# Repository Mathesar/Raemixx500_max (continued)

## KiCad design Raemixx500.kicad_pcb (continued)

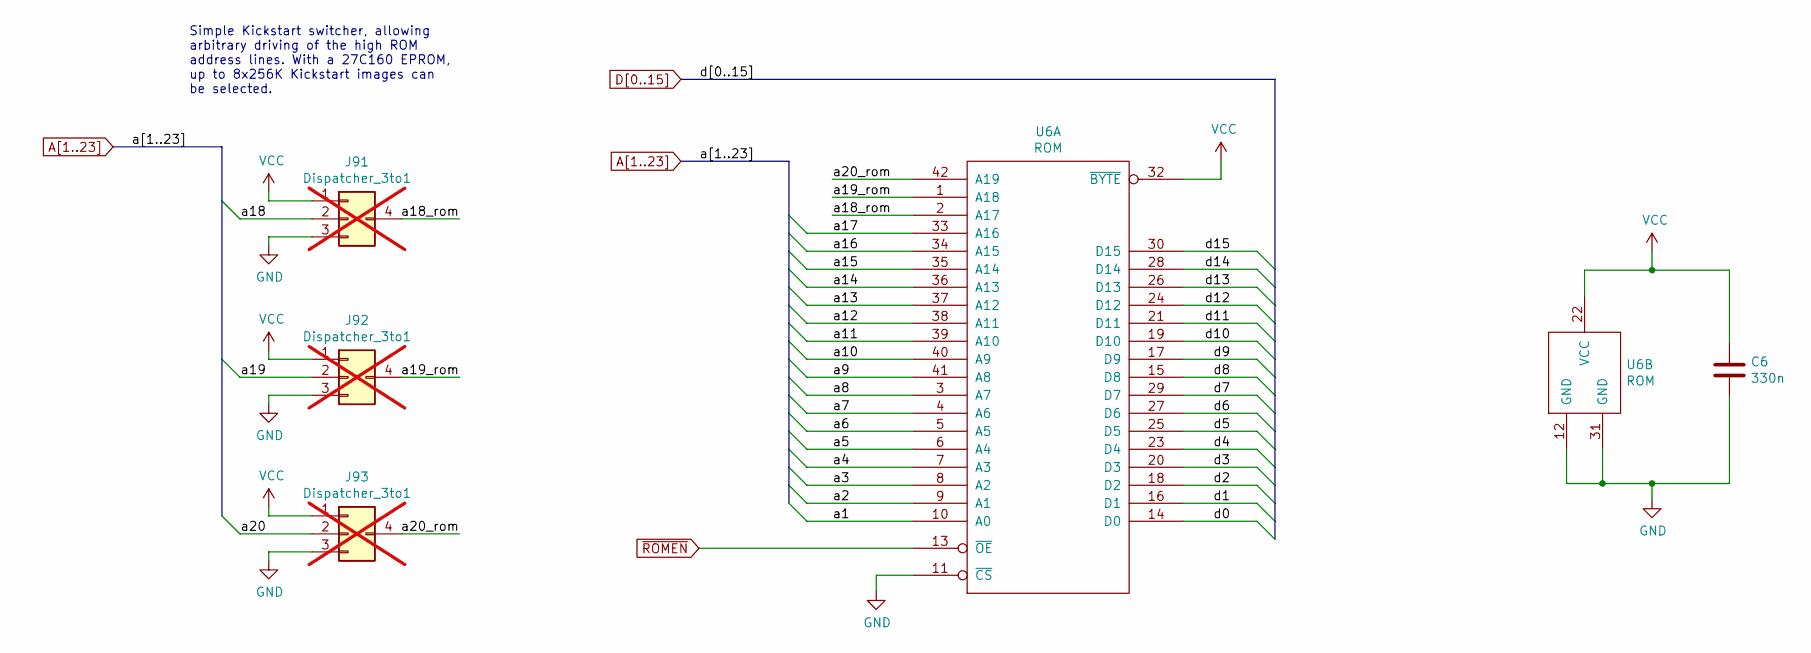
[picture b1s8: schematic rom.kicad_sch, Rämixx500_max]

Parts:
C6: 330n; C_Axial_L6.3mm_D2.5mm_P10.16mm; MFG Part Num C440C334K5R5TA7200; Mouser 80-C440C334K5R-TR
J91, J92, J93: Dispatcher_3to1; not fitted
U6: ROM; DIP-42_W15.24mm_Socket_LongPads; MFG Part Num 4842-6000-CP; Mouser 517-4842-6000-CP

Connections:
/Kickstart ROM/a18_rom: J91.4 (Out), U6.2 (A17)
/Kickstart ROM/a19_rom: J92.4 (Out), U6.1 (A18)
/Kickstart ROM/a20_rom: J93.4 (Out), U6.42 (A19)
A1: U6.10 (A0); also elsewhere on the board
A2: U6.9 (A1); also elsewhere on the board
A3: U6.8 (A2); also elsewhere on the board
A4: U6.7 (A3); also elsewhere on the board
A5: U6.6 (A4); also elsewhere on the board
A6: U6.5 (A5); also elsewhere on the board
A7: U6.4 (A6); also elsewhere on the board
A8: U6.3 (A7); also elsewhere on the board
A9: U6.41 (A8); also elsewhere on the board
A10: U6.40 (A9); also elsewhere on the board
A11: U6.39 (A10); also elsewhere on the board
A12: U6.38 (A11); also elsewhere on the board
A13: U6.37 (A12); also elsewhere on the board
A14: U6.36 (A13); also elsewhere on the board
A15: U6.35 (A14); also elsewhere on the board
A16: U6.34 (A15); also elsewhere on the board
A17: U6.33 (A16); also elsewhere on the board
A18: J91.2 (In_2); also elsewhere on the board
A19: J92.2 (In_2); also elsewhere on the board
A20: J93.2 (In_2); also elsewhere on the board
D0: U6.14 (D0); also elsewhere on the board
D1: U6.16 (D1); also elsewhere on the board
D2: U6.18 (D2); also elsewhere on the board
D3: U6.20 (D3); also elsewhere on the board
D4: U6.23 (D4); also elsewhere on the board
D5: U6.25 (D5); also elsewhere on the board
D6: U6.27 (D6); also elsewhere on the board
D7: U6.29 (D7); also elsewhere on the board
D8: U6.15 (D8); also elsewhere on the board
D9: U6.17 (D9); also elsewhere on the board
D10: U6.19 (D10); also elsewhere on the board
D11: U6.21 (D11); also elsewhere on the board
D12: U6.24 (D12); also elsewhere on the board
D13: U6.26 (D13); also elsewhere on the board
D14: U6.28 (D14); also elsewhere on the board
D15: U6.30 (D15); also elsewhere on the board
GND: C6.2, J91.3 (In_3), J92.3 (In_3), J93.3 (In_3), U6.11 (~CS), U6.12 (GND), U6.31 (GND); also elsewhere on the board
VCC: C6.1, J91.1 (In_1), J92.1 (In_1), J93.1 (In_1), U6.22 (VCC), U6.32 (~BYTE); also elsewhere on the board
~ROMEN: U6.13 (~OE); also elsewhere on the board

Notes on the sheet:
Simple Kickstart switcher, allowing arbitrary driving of the high ROM address lines. With a 27C160 EPROM, up to 8x256K Kickstart images can be selected.

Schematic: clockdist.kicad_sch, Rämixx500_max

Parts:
C33: 10n; C_Axial_L6.3mm_D2.5mm_P10.16mm; MFG Part Num C410C103K1R5TA; Mouser 80-C410C103K1R
E102, E103, E106, E107, E108: 47p; C_Axial_L9.0mm_D3.2mm_P12.70mm; MFG Part Num A470J15C0GF5TAA; Mouser 594-A470J15C0GF5TAA
E104, E105: 68; EMI_Filter_Long; MFG Part Num MFR-25FBF52-68R; Mouser 603-MFR-25FBF52-68R
E109, E791, E792, E793, E794: 47p; C_Axial_L6.3mm_D2.5mm_P10.16mm; MFG Part Num A470J15C0GF5TAA; Mouser 594-A470J15C0GF5TAA
E407: 10n; EMI_Filter_Short; MFG Part Num DSS1NB32A103Q91A; Mouser 81-DSS1NB32A103Q91A
RP103: 39; R_Array_SIP10; MFG Part Num 4610X-102-390LF; Mouser 652-4610X-2LF-39
U33: 74F258; DIP-16_W7.62mm_LongPads; MFG Part Num SN74F258N; Mouser 595-SN74F258N

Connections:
7MHZ: E103.1; also elsewhere on the board
7MHZ_A: E794.1; also elsewhere on the board
CCK: E108.1, U33.5, U33.6; also elsewhere on the board
CCKQ: E107.1, U33.10, U33.11; also elsewhere on the board
CDAC: E793.1, RP103.4 (R2.2); also elsewhere on the board
GND: C33.2, E102.2, E103.2, E104.2, E105.2, E106.2, E107.2, E108.2, E109.2, E407.2, E791.2, E792.2, E793.2, E794.2, U33.8 (GND), U33.15 (OE); also elsewhere on the board
unnamed: RP103.3 (R2.1), U33.4
unnamed: E104.1, RP103.5 (R3.1), U33.7
unnamed: E105.1, RP103.7 (R4.1), U33.9
unnamed: C33.1, E407.3, U33.16 (VCC)
VCC: E407.1; also elsewhere on the board
~CCKQ_A: E105.3, E109.1; also elsewhere on the board
~CCKQ: E791.1, RP103.8 (R4.2); also elsewhere on the board
~CCK_A: E102.1, E104.3; also elsewhere on the board
~CCK: E792.1, RP103.6 (R3.2); also elsewhere on the board
~CDAC: E106.1, U33.2, U33.3; also elsewhere on the board
~XCLKEN: U33.1 (S); also elsewhere on the board

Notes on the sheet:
FCC GOOBERS

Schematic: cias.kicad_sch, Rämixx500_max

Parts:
C7, C8: 10n; C_Axial_L6.3mm_D2.5mm_P10.16mm; MFG Part Num C410C103K1R5TA; Mouser 80-C410C103K1R
C39, C713: 10n; C_Axial_L9.0mm_D3.2mm_P12.70mm; MFG Part Num C410C103K1R5TA; Mouser 80-C410C103K1R
C42: 330n; C_Axial_L6.3mm_D2.5mm_P10.16mm; MFG Part Num C440C334K5R5TA7200; Mouser 80-C440C334K5R-TR
C501, C502: 330n; C_Axial_L9.0mm_D3.2mm_P12.70mm; MFG Part Num C440C334K5R5TA7200; Mouser 80-C440C334K5R-TR
C711: 100n; C_Axial_L9.0mm_D3.2mm_P12.70mm; MFG Part Num A104K15X7RF5TAA; Mouser 594-A104K15X7RF5TAA
C712: 10u; CP_Radial_D5.0mm_P2.50mm; MFG Part Num ECA-1EM100I; Mouser 667-ECA-1EM100I
CN6: SERIAL_DB25M; DB_25M; MFG Part Num L717SDB25PA4CH4F; Mouser 523-L717SDB25PA4CH4F
CN7: PARALLEL_DB25F; DB_25F; MFG Part Num L77SDB25SA4CH4F; Mouser 523-L77SDB25SA4CH4F
CN13: KEYBOARD; Keyboard_Connector; MFG Part Num 10129378-908003BLF; Mouser 649-1012937890803BLF
D501: 1N4148; D_DO-35_SOD27_P12.70mm_Horizontal; MFG Part Num 1N4148TR; Mouser 512-1N4148TR
E501, E502, E503: 47 1/2W; EMI_Filter_Longer; MFG Part Num PR01000104709JA500; Mouser 594-PR01000104709JA5
E511, E512, E513, E514, E515, E516, E517, E518, E519, E521, E522, E523, E524, E631, E632: 100p; EMI_Filter_Short; MFG Part Num DSS1NB32A101Q91A; Mouser 81-DSS1NB32A101Q91A
E520, E531, E533, E535, E536, E537, E538: 470p; EMI_Filter_Short; MFG Part Num DSS1NB32A471Q91A; Mouser 81-DSS1NB32A471Q91A
E532, E534: 150p; EMI_Filter_Short; MFG Part Num DSS1NB32A151Q91A; Mouser 81-DSS1NB32A151Q91A
J90: DRIVE_SWITCHER; DriveSwitchHeader; not fitted
J99: HD_ACT; PinHeader_1x02_P2.54mm_Vertical; MFG Part Num 10129378-902003BLF; Mouser 649-1012937890203BLF
JP1: Jumper_2_Bridged; Jumper2-Bridged; MFG Part Num SKIP
JP7B1: Jumper_3_Bridged23; Jumper3-Bridged23; MFG Part Num SKIP
Q501, Q504, Q711: 2N3904; TO-92L_Inline_Wide; MFG Part Num 2N3904BU; Mouser 512-2N3904BU
Q502, Q503: 2N3906; TO-92L_Inline_Wide; MFG Part Num 2N3906BU; Mouser 512-2N3906BU
R109: 68; R_Axial_DIN0309_L9.0mm_D3.2mm_P12.70mm_Horizontal; MFG Part Num MFR-25FBF52-68R; Mouser 603-MFR-25FBF52-68R
R501, R504, R505, R506, R509, R510: 10K; R_Axial_DIN0309_L9.0mm_D3.2mm_P12.70mm_Horizontal; MFG Part Num MFR-25FBF52-10K; Mouser 603-MFR-25FBF52-10K
R502: 2.7k; R_Axial_DIN0309_L9.0mm_D3.2mm_P12.70mm_Horizontal; MFG Part Num MFR-25FBF52-2K7; Mouser 603-MFR-25FBF52-2K7
R503, R508: 4.7k; R_Axial_DIN0309_L9.0mm_D3.2mm_P12.70mm_Horizontal; MFG Part Num MFR-25FBF52-4K7; Mouser 603-MFR-25FBF52-4K7
R507: 100; R_Axial_DIN0309_L9.0mm_D3.2mm_P12.70mm_Horizontal; MFG Part Num MFR-25FBF52-100R; Mouser 603-MFR-25FBF52-100R
R711: 1M; R_Axial_DIN0309_L9.0mm_D3.2mm_P12.70mm_Horizontal; MFG Part Num MFR-25FBF52-1M; Mouser 603-MFR-25FBF52-1M
R712: 47k; R_Axial_DIN0309_L9.0mm_D3.2mm_P12.70mm_Horizontal; MFG Part Num MFR-25FBF52-47K; Mouser 603-MFR-25FBF52-47K
R713: 1k; R_Axial_DIN0309_L9.0mm_D3.2mm_P12.70mm_Horizontal; MFG Part Num MFR-25FBF52-1K; Mouser 603-MFR-25FBF52-1K
RP501: 10K; R_Array_SIP10; MFG Part Num 4610X-101-103LF; Mouser 652-4610X-1LF-10K
U7, U8: VIA_8520; DIP-40_W15.24mm_Socket_LongPads; MFG Part Num 4840-6000-CP; Mouser 517-4840-6000-CP
U38: MC1488; DIP-14_W7.62mm_LongPads; MFG Part Num SN75C188N; Mouser 595-SN75C188N
U39: MC1489; DIP-14_W7.62mm_LongPads; MFG Part Num SN75C189N; Mouser 595-SN75C189N
U42: NE555; DIP-8_W7.62mm_LongPads; MFG Part Num SA555P; Mouser 595-SA555P

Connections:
+12V: E502.1, U38.14 (VCC); also elsewhere on the board
-12V: E503.1, U38.1 (VEE); also elsewhere on the board
/Parallel & Serial/+v: CN6.9, E502.3
/Parallel & Serial/-v: CN6.10, E503.3
/Parallel & Serial/cd: CN6.8, E537.3
/Parallel & Serial/clock: CN13.1, E632.1
/Parallel & Serial/cts: CN6.5, E535.3
/Parallel & Serial/data: CN13.2, E631.1
/Parallel & Serial/dsr: CN6.6, E536.3
/Parallel & Serial/dtr: CN6.20, E531.3
/Parallel & Serial/inuse: CN13.8, Q503.3 (C)
/Parallel & Serial/pp0: E512.1, U7.10 (PB0)
/Parallel & Serial/pp1: E513.1, U7.11 (PB1)
/Parallel & Serial/pp2: E514.1, U7.12 (PB2)
/Parallel & Serial/pp3: E515.1, U7.13 (PB3)
/Parallel & Serial/pp4: E516.1, U7.14 (PB4)
/Parallel & Serial/pp5: E517.1, U7.15 (PB5)
/Parallel & Serial/pp6: E518.1, U7.16 (PB6)
/Parallel & Serial/pp7: E519.1, U7.17 (PB7)
/Parallel & Serial/rts: CN6.4, E533.3
/Parallel & Serial/rxd: CN6.3, E534.3
/Parallel & Serial/sel0_out: J90.1, J90.2, U8.13 (PB3)
/Parallel & Serial/sel1_out: J90.5, J90.6, U8.14 (PB4)
/Parallel & Serial/status: CN13.7, Q502.3 (C), R507.1
/Parallel & Serial/txd: CN6.2, E532.3
/Parallel & Serial/~auto: CN7.14, E501.3
/Parallel & Serial/~init: CN7.16, E520.3
A8: U7.38 (RS0), U8.38 (RS0); also elsewhere on the board
A9: U7.37 (RS1), U8.37 (RS1); also elsewhere on the board
A10: U7.36 (RS2), U8.36 (RS2); also elsewhere on the board
A11: U7.35 (RS3), U8.35 (RS3); also elsewhere on the board
AUDIN: C501.1; also elsewhere on the board
AUDOUT: C502.2; also elsewhere on the board
D0: U7.33 (D0); also elsewhere on the board
D1: U7.32 (D1); also elsewhere on the board
D2: U7.31 (D2); also elsewhere on the board
D3: U7.30 (D3); also elsewhere on the board
D4: U7.29 (D4); also elsewhere on the board
D5: U7.28 (D5); also elsewhere on the board
D6: U7.27 (D6); also elsewhere on the board
D7: U7.26 (D7); also elsewhere on the board
D8: U8.33 (D0); also elsewhere on the board
D9: U8.32 (D1); also elsewhere on the board
D10: U8.31 (D2); also elsewhere on the board
D11: U8.30 (D3); also elsewhere on the board
D12: U8.29 (D4); also elsewhere on the board
D13: U8.28 (D5); also elsewhere on the board
D14: U8.27 (D6); also elsewhere on the board
D15: U8.26 (D7); also elsewhere on the board
DIR: U8.11 (PB1); also elsewhere on the board
E: R109.2; also elsewhere on the board
GND: C7.2, C8.2, C39.2, C42.2, C711.2, C712.2, C713.2, CN6.0 (PAD), CN6.7, CN7.0 (PAD), CN7.17, CN7.18, CN7.19, CN7.20, CN7.21, CN7.22, CN7.23, CN7.24, CN7.25, CN13.6, D501.2 (A), E501.2, E502.2, E503.2, E511.2, E512.2, E513.2, E514.2, E515.2, E516.2, E517.2, E518.2, E519.2, E520.2, E521.2, E522.2, E523.2, E524.2, E531.2, E532.2, E533.2, E534.2, E535.2, E536.2, E537.2, E538.2, E631.2, E632.2, Q501.1 (E), Q504.1 (E), Q711.1 (E), R501.1, R509.2, U7.1 (GND), U8.1 (GND), U38.7 (GND), U39.7 (GND), U42.1 (GND); also elsewhere on the board
unnamed: C502.1, CN6.11
unnamed: C501.2, CN6.18
unnamed: CN6.22, E538.3
unnamed: CN7.1, E511.3
unnamed: CN7.2, E512.3
unnamed: CN7.3, E513.3
unnamed: CN7.4, E514.3
unnamed: CN7.5, E515.3
unnamed: CN7.6, E516.3
unnamed: CN7.7, E517.3
unnamed: CN7.8, E518.3
unnamed: CN7.9, E519.3
unnamed: CN7.10, E521.3
unnamed: CN7.11, E522.3
unnamed: CN7.12, E523.3
unnamed: CN7.13, E524.3
unnamed: D501.1 (K), Q501.2 (B), R501.2, R502.2
unnamed: E538.1, R502.1
unnamed: J99.1, Q504.3 (C), R508.2
unnamed: J99.2, R510.2
unnamed: JP1.1 (A), Q711.3 (C)
unnamed: JP7B1.2 (C), U7.19 (TICK)
unnamed: E524.1, Q501.3 (C), RP501.4 (R3), U8.4 (PA2)
unnamed: Q502.2 (B), R503.1
unnamed: Q504.2 (B), R509.1, R510.1
unnamed: Q711.2 (B), R713.1
unnamed: E521.1, RP501.6 (R5), U7.24 (~F)
unnamed: E511.1, RP501.10 (R9), U7.18 (~PC)
unnamed: R109.1, U7.25 (E), U8.25 (E)
unnamed: E523.1, U8.3 (PA1), U8.40 (C)
unnamed: E522.1, U8.2 (PA0), U8.39 (S)
unnamed: U8.8 (PA6), U38.4 (IN1_B)
unnamed: E533.1, U38.6 (OUT_B)
unnamed: E532.1, U38.8 (OUT_C)
unnamed: U8.9 (PA7), U38.12 (IN2_D)
unnamed: E531.1, U38.11 (OUT_D)
unnamed: E534.1, U39.1 (IN_A)
unnamed: E535.1, U39.4 (IN_B)
unnamed: U8.6 (PA4), U39.6 (OUT_B)
unnamed: E536.1, U39.10 (IN_C)
unnamed: U8.5 (PA3), U39.8 (OUT_C)
unnamed: E537.1, U39.13 (IN_D)
unnamed: U8.7 (PA5), U39.11 (OUT_D)
unnamed: C713.1, U42.5 (CV)
unnamed: C712.1, R712.1, U42.6 (THR), U42.7 (DIS)
unnamed: R713.2, U42.3 (Q)
unnamed: C711.1, R711.1, U42.2 (TR)
OVL: U7.2 (PA0); also elsewhere on the board
R~W: U7.22 (~W), U8.22 (~W); also elsewhere on the board
VCC: C7.1, C8.1, C39.1, C42.1, CN13.4, E501.1, Q502.1 (E), Q503.1 (E), R505.2, R506.2, R507.2, R711.2, R712.2, RP501.1 (common), U7.20 (VCC), U8.20 (VCC), U38.5 (IN2_B), U38.10 (IN1_C), U38.13 (IN1_D), U39.14 (VCC), U42.4 (R), U42.8 (VCC); also elsewhere on the board
~CHNG: U7.4 (PA2); also elsewhere on the board
~DRVLED: Q503.2 (B), R504.1, R508.1
~EVEN_CIA: U8.23 (~CS); also elsewhere on the board
~EXTICK: JP7B1.1 (A), RP501.9 (R8); also elsewhere on the board
~FIRE0: U7.8 (PA6); also elsewhere on the board
~FIRE1: U7.9 (PA7); also elsewhere on the board
~HSYNC: U8.19 (TICK); also elsewhere on the board
~INDEX: RP501.7 (R6), U8.24 (~F); also elsewhere on the board
~INT2: U7.21 (~INT); also elsewhere on the board
~INT6: U8.21 (~INT); also elsewhere on the board
~IORESET: E520.1; also elsewhere on the board
~KBCLOCK: E632.3, RP501.2 (R1), U7.40 (C)
~KBDATA: E631.3, RP501.3 (R2), U7.39 (S)
~KBRESET: CN13.3, JP1.2 (B), RP501.5 (R4); also elsewhere on the board
~LED: R503.2, R505.1, U7.3 (PA1); also elsewhere on the board
~MTR0: R504.2, R506.1; also elsewhere on the board
~MTR: U8.17 (PB7); also elsewhere on the board
~ODD_CIA: U7.23 (~CS); also elsewhere on the board
~RDY: U7.7 (PA5); also elsewhere on the board
~RESET: U7.34 (~RESET), U8.34 (~RESET); also elsewhere on the board
~RXD: U39.3 (OUT_A); also elsewhere on the board
~SEL0: J90.3; also elsewhere on the board
~SEL1: J90.4; also elsewhere on the board
~SEL2: U8.15 (PB5); also elsewhere on the board
~SEL3: U8.16 (PB6); also elsewhere on the board
~SIDE: U8.12 (PB2); also elsewhere on the board
~STEP: U8.10 (PB0); also elsewhere on the board
~TRK0: U7.6 (PA4); also elsewhere on the board
~TXD: U38.9 (IN2_C); also elsewhere on the board
~VSYNC: JP7B1.3 (B); also elsewhere on the board
~WPROT: U7.5 (PA3); also elsewhere on the board

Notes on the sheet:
rxc
ADDITIONAL CIRCUITRY TO BLINK THE FLOPPY LED ON HARD DISK ACTIVITY. PIN 1 IS A 5V COMPATIBLE ACTIVE LOW INPUT. PIN 2 IS A 3.3V/5V COMPATIBLE ACTIVE HIGH INPUT. EXAMPLE USAGES: CONNECT J99 PIN1 TO PIN 39 OF CF ADAPTERS OR ALTERNATIVELY CONNECT J99 PIN 2 TO J2 PIN 1 OF THE A500-SD-PLUS CONTROLLER
Simple implementation of a floppy drive switcher that will allow using the first external drive as DF0:. The internal drive will not be accessible in this case.
~{EXTICK} is not connected here in original schematics, but it is on the actual board.
scts
srts
stxd
KEYBOARD CONNECTOR
POWER
clk
srxd
scd
POWER-UP RESET
txc
THIS CONNECTION IS MISSING ON THE ORIGINAL SCHEMATICS BUT PRESENT ON ACTUAL BOARDS! (THANKS LIV2)
sqd
RS232 DECOUPLING
PARALLEL PORT
~{err}
RS232

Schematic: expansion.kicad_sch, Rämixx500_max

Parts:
E702, E703, E704: 10n; EMI_Filter_Short; MFG Part Num DSS1NB32A103Q91A; Mouser 81-DSS1NB32A103Q91A
P1: EXPANSION BUS; A500_SIDE_SLOT; MFG Part Num SKIP

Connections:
7MHZ: P1.7 (7MHZ); also elsewhere on the board
+12V: E704.1; also elsewhere on the board
-12V: E703.1; also elsewhere on the board
A1: P1.29 (A1); also elsewhere on the board
A2: P1.27 (A2); also elsewhere on the board
A3: P1.26 (A3); also elsewhere on the board
A4: P1.24 (A4); also elsewhere on the board
A5: P1.21 (A5); also elsewhere on the board
A6: P1.23 (A6); also elsewhere on the board
A7: P1.28 (A7); also elsewhere on the board
A8: P1.30 (A8); also elsewhere on the board
A9: P1.32 (A9); also elsewhere on the board
A10: P1.34 (A10); also elsewhere on the board
A11: P1.36 (A11); also elsewhere on the board
A12: P1.38 (A12); also elsewhere on the board
A13: P1.39 (A13); also elsewhere on the board
A14: P1.41 (A14); also elsewhere on the board
A15: P1.43 (A15); also elsewhere on the board
A16: P1.45 (A16); also elsewhere on the board
A17: P1.47 (A17); also elsewhere on the board
A18: P1.52 (A18); also elsewhere on the board
A19: P1.54 (A19); also elsewhere on the board
A20: P1.56 (A20); also elsewhere on the board
A21: P1.58 (A21); also elsewhere on the board
A22: P1.57 (A22); also elsewhere on the board
A23: P1.59 (A23); also elsewhere on the board
CDAC: P1.15 (~CDAC); also elsewhere on the board
D0: P1.75 (D0); also elsewhere on the board
D1: P1.77 (D1); also elsewhere on the board
D2: P1.79 (D2); also elsewhere on the board
D3: P1.81 (D3); also elsewhere on the board
D4: P1.83 (D4); also elsewhere on the board
D5: P1.86 (D5); also elsewhere on the board
D6: P1.84 (D6); also elsewhere on the board
D7: P1.82 (D7); also elsewhere on the board
D8: P1.80 (D8); also elsewhere on the board
D9: P1.78 (D9); also elsewhere on the board
D10: P1.76 (D10); also elsewhere on the board
D11: P1.71 (D11); also elsewhere on the board
D12: P1.69 (D12); also elsewhere on the board
D13: P1.67 (D13); also elsewhere on the board
D14: P1.65 (D14); also elsewhere on the board
D15: P1.63 (D15); also elsewhere on the board
E: P1.50 (E); also elsewhere on the board
FC0: P1.31 (FC0); also elsewhere on the board
FC1: P1.33 (FC1); also elsewhere on the board
FC2: P1.35 (FC2); also elsewhere on the board
GND: E702.2, E703.2, E704.2, P1.1 (GND), P1.2 (GND), P1.3 (GND), P1.4 (GND), P1.12 (~CONFIG), P1.13 (GND), P1.25 (GND), P1.37 (GND), P1.49 (GND), P1.61 (GND), P1.73 (GND), P1.85 (GND); also elsewhere on the board
unnamed: E702.3, P1.5 (VCC), P1.6 (VCC)
unnamed: E704.3, P1.10 (+12V)
unnamed: E703.3, P1.8 (-12V)
R~W: P1.68 (R~W); also elsewhere on the board
VCC: E702.1; also elsewhere on the board
XRDY: P1.18 (XRDY); also elsewhere on the board
~AS: P1.74 (~AS); also elsewhere on the board
~BEER: P1.46 (~BERR); also elsewhere on the board
~BGACK: P1.62 (~BGACK); also elsewhere on the board
~BG: P1.64 (~BG); also elsewhere on the board
~BR: P1.60 (~BR); also elsewhere on the board
~CCKQ: P1.14 (~CCKQ); also elsewhere on the board
~CCK: P1.16 (~CCK); also elsewhere on the board
~DTACK: P1.66 (~DTACK); also elsewhere on the board
~HLT: P1.55 (~HALT); also elsewhere on the board
~INT2: P1.19 (~INT2); also elsewhere on the board
~INT6: P1.22 (~INT6); also elsewhere on the board
~IPL0: P1.40 (~IPL0); also elsewhere on the board
~IPL1: P1.42 (~IPL1); also elsewhere on the board
~IPL2: P1.44 (~IPL2); also elsewhere on the board
~LDS: P1.70 (~LDS); also elsewhere on the board
~OVR: P1.17 (~OVR); also elsewhere on the board
~RST: P1.53 (~RESET); also elsewhere on the board
~UDS: P1.72 (~UDS); also elsewhere on the board
~VMA: P1.51 (~VMA); also elsewhere on the board
~VPA: P1.48 (~VPA); also elsewhere on the board

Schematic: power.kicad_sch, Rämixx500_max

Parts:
C1, C2, C5, C11, C13, C14, C804: 330n; C_Axial_L6.3mm_D2.5mm_P10.16mm; MFG Part Num C440C334K5R5TA7200; Mouser 80-C440C334K5R-TR
C10, C12, C32, C34, C35, C36, C37, C701, C800, C801, C802, C803: 10n; C_Axial_L6.3mm_D2.5mm_P10.16mm; MFG Part Num C410C103K1R5TA; Mouser 80-C410C103K1R
C811, C812, C813, C814, C815, C816: 100u; CP_Radial_D8.0mm_P5.00mm; MFG Part Num ECA-1VM101B; Mouser 667-ECA-1VM101B
C821, C822: 47u; CP_Radial_D8.0mm_P5.00mm; MFG Part Num ECA-1VM470B; Mouser 667-ECA-1VM470B
CN8: POWER; DS215+DIN8_COMBO; MFG Part Num 252167-01
E101, E110: 10n; EMI_Filter_Short; MFG Part Num DSS1NB32A103Q91A; Mouser 81-DSS1NB32A103Q91A
LF1: L; LineFilter; not fitted
LF99: CM4545Z131B-10; MFG Part Num CM4545Z131B-10; Mouser 875-CM4545Z131B-10
MT1, MT2, MT4, MT5, MT6, MT7: MountingHole_Pad; MountingHole_4mm_Pad; MFG Part Num SKIP
U1: 68000D; DIP-64_W22.86mm_Socket_LongPads; MFG Part Num 110-93-964-41-001000; Mouser 575-193964
U2: FAT_AGNUS_8375; PLCC-84_THT-Socket; MFG Part Num 940-44-084-24-000000; Mouser 575-948424
U5: GARY_5719; DIP-48_W15.24mm_Socket_LongPads; MFG Part Num 4848-6000-CP; Mouser 517-4848-6000-CP
U10, U12: 74LS244; DIP-20_W7.62mm_LongPads; MFG Part Num SN74LS244N; Mouser 595-SN74LS244N
U11, U13: 74LS373; DIP-20_W7.62mm_LongPads; MFG Part Num SN74LS373N; Mouser 595-SN74LS373N
U32: 74F139; DIP-16_W7.62mm_LongPads; MFG Part Num CD74ACT139E; Mouser 595-CD74ACT139E
U34, U35: 74F244; DIP-20_W7.62mm_LongPads; MFG Part Num SN74F244N; Mouser 595-SN74F244N
U36: 74LS05; DIP-14_W7.62mm_LongPads; MFG Part Num SN74LS05N; Mouser 595-SN74LS05N
U37: 74LS32; DIP-14_W7.62mm_LongPads; MFG Part Num SN74LS32N; Mouser 595-SN74LS32N
X1: XTAL; Oscillator_DIP-14

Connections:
+12V: C802.1, C821.1, LF1.5, LF99.5; also elsewhere on the board
-12V: C803.2, C822.2, LF1.6, LF99.6; also elsewhere on the board
GND: C1.2, C2.2, C5.2, C10.2, C11.2, C12.2, C13.2, C14.2, C32.2, C34.2, C35.2, C36.2, C37.2, C701.2, C801.2, C802.2, C803.1, C804.2, C811.2, C812.2, C813.2, C814.2, C815.2, C816.2, C821.2, C822.1, CN8.2 (SH1), CN8.6 (SH2), E101.2, E110.2, LF1.8, LF99.8, MT1.1, MT2.1, MT4.1, MT5.1, MT6.1, MT7.1, U1.16 (GND), U1.53 (GND), U2.41 (GND), U2.58 (GND), U2.82 (GND), U5.1 (GND), U5.24 (GND), U5.40 (GND), U10.10 (GND), U11.10 (GND), U12.10 (GND), U13.10 (GND), U32.8 (GND), U34.10 (GND), U35.10 (GND), U36.7 (GND), U37.7 (GND), X1.1 (~EN), X1.7 (GND); also elsewhere on the board
unnamed: C800.2, CN8.1 (+5V), LF1.2, LF99.2
unnamed: CN8.3 (+12V), LF1.4, LF99.4
unnamed: CN8.5 (-12V), LF1.3, LF99.3
unnamed: C800.1, CN8.4 (GND), LF1.1, LF99.1
unnamed: C2.1, E101.3, U2.15 (VCC)
unnamed: C701.1, E110.3, X1.14 (VDD)
VCC: C1.1, C5.1, C10.1, C11.1, C12.1, C13.1, C14.1, C32.1, C34.1, C35.1, C36.1, C37.1, C801.1, C804.1, C811.1, C812.1, C813.1, C814.1, C815.1, C816.1, E101.1, E110.1, LF1.7, LF99.7, U1.14 (VCC), U1.49 (VCC), U5.6 (VCC), U5.17 (VCC), U5.48 (VCC), U10.20 (VCC), U11.20 (VCC), U12.20 (VCC), U13.20 (VCC), U32.16 (VCC), U34.20 (VCC), U35.20 (VCC), U36.14 (VCC), U37.14 (VCC); also elsewhere on the board

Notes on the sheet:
GROUNDED HOLES
ALTERNATIVE FOOTPRINT FOR MODERN LF1 EQUIVALENT
POWER INPUT
The original Amiga power socket and plug were made by Power Dynamics. The power socket is a DS-215 and the power plug is a DP-215. Note: This is the pinout of the MALE connector on the CABLE's end (DP-215)!

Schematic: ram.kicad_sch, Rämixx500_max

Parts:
C16, C17, C21: 10n; C_Axial_L6.3mm_D2.5mm_P10.16mm; MFG Part Num C410C103K1R5TA; Mouser 80-C410C103K1R
C18, C19, C20: 330n; C_Axial_L6.3mm_D2.5mm_P10.16mm; MFG Part Num C440C334K5R5TA7200; Mouser 80-C440C334K5R-TR
JP201: Jumper_3_Bridged23; Jumper3-Bridged23; MFG Part Num SKIP
R201, R204, R205: 4.7k; R_Axial_DIN0309_L9.0mm_D3.2mm_P12.70mm_Horizontal; MFG Part Num MFR-25FBF52-4K7; Mouser 603-MFR-25FBF52-4K7
R206, R207, R208, R209, R210: 68; R_Axial_DIN0309_L9.0mm_D3.2mm_P12.70mm_Horizontal; MFG Part Num MFR-25FBF52-68R; Mouser 603-MFR-25FBF52-68R
RP201, RP202, RP203: 68; R_Array_SIP10; MFG Part Num 4610X-102-680LF; Mouser 652-4610X-2LF-68
U16: SIMM; SIMM_TE_Connectivity_5822134-3; MFG Part Num 5822134-3; Mouser 571-5822134-3
U17: 74F08; DIP-14_W7.62mm_LongPads; MFG Part Num SN74F08N; Mouser 595-SN74F08N
U18: 74F74; DIP-14_W7.62mm_LongPads; MFG Part Num SN74F74N; Mouser 595-SN74F74N
U19: 74F00; DIP-14_W7.62mm_LongPads; MFG Part Num SN74F00N; Mouser 595-SN74F00N
U32: 74F139; DIP-16_W7.62mm_LongPads; MFG Part Num CD74ACT139E; Mouser 595-CD74ACT139E
U34, U35: 74F244; DIP-20_W7.62mm_LongPads; MFG Part Num SN74F244N; Mouser 595-SN74F244N

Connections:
/RAM/MA0: RP201.2 (R1.2), U16.12 (A0)
/RAM/MA1: RP201.4 (R2.2), U16.13 (A1)
/RAM/MA2: RP201.6 (R3.2), U16.14 (A2)
/RAM/MA3: RP201.8 (R4.2), U16.15 (A3)
/RAM/MA4: RP201.10 (R5.2), U16.16 (A4)
/RAM/MA5: RP202.4 (R2.2), U16.17 (A5)
/RAM/MA6: RP202.10 (R5.2), U16.18 (A6)
/RAM/MA7: RP202.8 (R4.2), U16.28 (A7)
/RAM/MA8: RP202.2 (R1.2), U16.31 (A8)
/RAM/MA9: RP202.6 (R3.2), U16.32 (A9)
A19: U17.1; also elsewhere on the board
A20: U17.2; also elsewhere on the board
A23: U17.5, U17.9, U19.5; also elsewhere on the board
BDRA0: RP201.1 (R1.1), U34.9 (O0b); also elsewhere on the board
BDRA1: RP201.3 (R2.1), U34.12 (O3a); also elsewhere on the board
BDRA2: RP201.5 (R3.1), U34.7 (O1b); also elsewhere on the board
BDRA3: RP201.7 (R4.1), U34.14 (O2a); also elsewhere on the board
BDRA4: RP201.9 (R5.1), U34.5 (O2b); also elsewhere on the board
BDRA5: RP202.3 (R2.1), U34.16 (O1a); also elsewhere on the board
BDRA6: RP202.9 (R5.1), U34.3 (O3b); also elsewhere on the board
BDRA7: RP202.7 (R4.1), U34.18 (O0a); also elsewhere on the board
BDRA8: RP202.1 (R1.1), U35.9 (O0b); also elsewhere on the board
BDRA9: RP202.5 (R3.1), U35.16 (O1a); also elsewhere on the board
CCKQ: U18.11 (C); also elsewhere on the board
DRA0: U34.11 (I0b); also elsewhere on the board
DRA1: U34.8 (I3a); also elsewhere on the board
DRA2: U34.13 (I1b); also elsewhere on the board
DRA3: U34.6 (I2a); also elsewhere on the board
DRA4: U34.15 (I2b); also elsewhere on the board
DRA5: U34.4 (I1a); also elsewhere on the board
DRA6: U34.17 (I3b); also elsewhere on the board
DRA7: U34.2 (I0a); also elsewhere on the board
DRA8: U35.11 (I0b); also elsewhere on the board
DRA9: U35.4 (I1a); also elsewhere on the board
DRD0: U16.49 (DQ9), U16.50 (DQ25); also elsewhere on the board
DRD1: U16.51 (DQ10), U16.52 (DQ26); also elsewhere on the board
DRD2: U16.53 (DQ11), U16.54 (DQ27); also elsewhere on the board
DRD3: U16.55 (DQ12), U16.56 (DQ28); also elsewhere on the board
DRD4: U16.57 (DQ13), U16.58 (DQ29); also elsewhere on the board
DRD5: U16.60 (DQ30), U16.61 (DQ14); also elsewhere on the board
DRD6: U16.62 (DQ31), U16.63 (DQ15); also elsewhere on the board
DRD7: U16.64 (DQ32), U16.65 (DQ16); also elsewhere on the board
DRD8: U16.26 (DQ8), U16.27 (DQ24); also elsewhere on the board
DRD9: U16.24 (DQ7), U16.25 (DQ23); also elsewhere on the board
DRD10: U16.22 (DQ6), U16.23 (DQ22); also elsewhere on the board
DRD11: U16.20 (DQ5), U16.21 (DQ21); also elsewhere on the board
DRD12: U16.8 (DQ4), U16.9 (DQ20); also elsewhere on the board
DRD13: U16.6 (DQ3), U16.7 (DQ19); also elsewhere on the board
DRD14: U16.4 (DQ2), U16.5 (DQ18); also elsewhere on the board
DRD15: U16.2 (DQ1), U16.3 (DQ17); also elsewhere on the board
GND: C16.2, C17.2, C18.2, C19.2, C20.2, C21.2, JP201.3 (B), U16.1 (VSS), U16.19 (A10), U16.29 (A11), U16.39 (VSS), U16.72 (VSS), U17.7 (GND), U18.1 (~R), U18.2 (D), U18.3 (C), U18.4 (~S), U18.7 (GND), U19.7 (GND), U34.1 (OEa), U34.19 (OEb), U35.1 (OEa), U35.8 (I3a), U35.17 (I3b), U35.19 (OEb); also elsewhere on the board
unnamed: JP201.1 (A), U18.9 (Q), U32.2 (A0), U32.14 (A0)
unnamed: JP201.2 (C), U32.3 (A1), U32.13 (A1)
unnamed: R209.1, U19.8
unnamed: R210.1, U19.11
unnamed: RP203.1 (R1.1), U35.18 (O0a)
unnamed: RP203.4 (R2.2), U32.12 (O0)
unnamed: RP203.6 (R3.2), U32.11 (O1)
unnamed: RP203.8 (R4.2), U32.5 (O1)
unnamed: RP203.10 (R5.2), U32.4 (O0)
unnamed: R205.1, U16.33 (~RAS3), U16.45 (~RAS1)
unnamed: U17.3, U17.4, U19.4
unnamed: U17.6, U19.13
unnamed: U17.8, U18.12 (D)
unnamed: U19.6, U19.9
unnamed: U19.3, U19.10, U19.12
unnamed: U32.1 (E), U35.7 (O1b)
unnamed: R207.1, U32.7 (O3)
unnamed: U32.15 (E), U35.5 (O2b)
unnamed: R208.1, U32.9 (O3)
unnamed: U17.11, U35.6 (I2a)
unnamed: R206.1, U35.14 (O2a)
PRDL: R201.2, U16.37 (PDQ2), U16.38 (PDQ4)
PRDU: R204.2, U16.35 (PDQ3), U16.36 (PDQ1)
VCC: C16.1, C17.1, C18.1, C19.1, C20.1, C21.1, R201.1, R204.1, R205.2, U16.10 (VCC), U16.30 (VCC), U16.59 (VCC), U17.14 (VCC), U18.10 (~S), U18.13 (~R), U18.14 (VCC), U19.14 (VCC); also elsewhere on the board
~BCASL0: RP203.9 (R5.1), U16.43 (~CAS1)
~BCASL1: RP203.7 (R4.1), U16.42 (~CAS3)
~BCASL3: R207.2; also elsewhere on the board
~BCASU0: RP203.3 (R2.1), U16.40 (~CAS0)
~BCASU1: RP203.5 (R3.1), U16.41 (~CAS2)
~BCASU3: R208.2; also elsewhere on the board
~BLIT: U17.10; also elsewhere on the board
~BRAS: R206.2, U16.34 (~RAS2), U16.44 (~RAS0); also elsewhere on the board
~BWE: RP203.2 (R1.2), U16.47 (~WE); also elsewhere on the board
~CASL: U35.13 (I1b); also elsewhere on the board
~CASU: U35.15 (I2b); also elsewhere on the board
~RAMEN_GARY: U19.2; also elsewhere on the board
~RAMEN: R209.2; also elsewhere on the board
~RAS0: U17.13; also elsewhere on the board
~RAS1: U17.12; also elsewhere on the board
~REGEN_GARY: U19.1; also elsewhere on the board
~REGEN: R210.2; also elsewhere on the board
~WE: U35.2 (I0a); also elsewhere on the board

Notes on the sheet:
SIMM must be at least 4MEG
parity pullups
SPARE
slow RAM select 1-2 trapdoor 2-3 SIMM (default)
ADDRESS A23 A20 A19 ~{RAMEN_G} ~{REGEN_G} ~{RAM_EN} ~{REG_EN} $000000 0 0 0 0 1 0 1 $080000 0 0 1 0 1 0 1 $100000 0 1 0 0 1 0 1 $180000 0 1 1 0 1 0 1 $C00000 1 0 0 0 1 0 1 $C80000 1 0 1 1 0 0 1 $D00000 1 1 0 1 0 0 1 $D80000 1 1 1 1 0 1 0

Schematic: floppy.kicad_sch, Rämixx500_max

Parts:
CN5: EXTFLOPPY_DB23F; DB_23F; MFG Part Num 390241-03
CN11: INTERNAL_FLOPPY; PinHeader_2x17_P2.54mm_Vertical; MFG Part Num 77313-101-34LF; Mouser 649-77313-101-34LF
CN12: FLOPPY_POWER; PinHeader_1x04_P2.54mm_Vertical; MFG Part Num 171825-4; Mouser 571-1718254
CN14: IDE_POWER; PinHeader_1x04_P2.54mm_Vertical; MFG Part Num SKIP; not fitted
CN15: IDE_I/F; PinHeader_1x04_P2.54mm_Vertical; MFG Part Num SKIP; not fitted
E601, E602: 10n; EMI_Filter_Long; MFG Part Num DSS1NB32A103Q91A; Mouser 81-DSS1NB32A103Q91A
E611, E612, E613, E614, E615, E616, E617, E618, E619, E620, E621, E622, E623, E624, E625, E626: 100p; EMI_Filter_Short; MFG Part Num DSS1NB32A101Q91A; Mouser 81-DSS1NB32A101Q91A
U5: GARY_5719; DIP-48_W15.24mm_Socket_LongPads; MFG Part Num 4848-6000-CP; Mouser 517-4848-6000-CP
U36: 74LS05; DIP-14_W7.62mm_LongPads; MFG Part Num SN74LS05N; Mouser 595-SN74LS05N

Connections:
+12V: CN12.4, CN14.4, E602.1; also elsewhere on the board
DIR: CN11.18, E623.1; also elsewhere on the board
DKWE: U5.8 (DKWE); also elsewhere on the board
GND: CN5.0 (PAD), CN5.3, CN5.4, CN5.5, CN5.6, CN5.7, CN11.1, CN11.5, CN11.7, CN11.9, CN11.11, CN11.13, CN11.15, CN11.17, CN11.19, CN11.21, CN11.23, CN11.25, CN11.27, CN11.29, CN11.31, CN11.33, CN12.2, CN12.3, CN14.2, CN14.3, CN15.4, E601.2, E602.2, E611.2, E612.2, E613.2, E614.2, E615.2, E616.2, E617.2, E618.2, E619.2, E620.2, E621.2, E622.2, E623.2, E624.2, E625.2, E626.2; also elsewhere on the board
unnamed: CN5.13, E617.3
unnamed: CN5.14, E618.3
unnamed: CN5.15, E619.3
unnamed: CN5.16, E620.3
unnamed: CN5.17, E621.3
unnamed: CN5.18, E622.3
unnamed: CN5.19, E623.3
unnamed: CN5.20, E624.3
unnamed: CN5.21, E625.3
unnamed: CN5.22, E626.3
unnamed: CN5.23, E602.3
unnamed: CN5.1, E611.3
unnamed: CN5.2, E612.3
unnamed: CN5.8, E613.3
unnamed: CN5.9, E614.3
unnamed: CN5.10, E615.3
unnamed: CN5.11, E616.3
unnamed: CN5.12, E601.3
unnamed: U5.45 (DKWDB), U36.5
unnamed: U5.44 (DKWEB), U36.9
unnamed: U5.46 (MTRON), U36.3
unnamed: U5.47 (MTRX), U36.1
VCC: CN12.1, CN14.1, E601.1; also elsewhere on the board
XRDY: CN15.3; also elsewhere on the board
~CHNG: CN11.2, E616.1; also elsewhere on the board
~DKRD: CN11.30, E612.1; also elsewhere on the board
~DKWDB: CN11.22, E621.1, U36.6
~DKWD: U5.9 (~DKWD); also elsewhere on the board
~DKWEB: CN11.24, E620.1, U36.8
~INDEX: CN11.8, E626.1; also elsewhere on the board
~INT2: CN15.1; also elsewhere on the board
~IORESET: E615.1; also elsewhere on the board
~KBRESET: U5.5 (~KBRESET); also elsewhere on the board
~MTR0: CN11.4, CN11.16, U36.4; also elsewhere on the board
~MTRX: E613.1, U36.2
~MTR: U5.7 (~MTR); also elsewhere on the board
~OVR: CN15.2; also elsewhere on the board
~RDY: CN11.34, E611.1; also elsewhere on the board
~SEL0: CN11.10, U5.16 (~SEL); also elsewhere on the board
~SEL1: CN11.12, E625.1; also elsewhere on the board
~SEL2: E614.1; also elsewhere on the board
~SEL3: E624.1; also elsewhere on the board
~SIDE: CN11.32, E617.1; also elsewhere on the board
~STEP: CN11.20, E622.1; also elsewhere on the board
~TRK0: CN11.26, E619.1; also elsewhere on the board
~WPROT: CN11.28, E618.1; also elsewhere on the board

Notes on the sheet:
These two are not normally populated on actual boards
EXTERNAL FLOPPY
